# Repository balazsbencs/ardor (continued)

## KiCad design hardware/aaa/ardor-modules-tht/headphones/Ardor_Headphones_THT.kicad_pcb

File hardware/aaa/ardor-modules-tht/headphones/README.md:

# Stereo headphones / LM386 / relay mute

T1 hand-assembly PCB: 96 × 84 mm. **Unbuilt engineering prototype.**

[KiCad project](Ardor_Headphones_THT.kicad_pro) · [Manual BOM](BOM.csv) · [Schematic](review/schematic.pdf) · [Bare-board Gerbers](assembly/Ardor_Headphones_THT-Gerbers.zip)

Supply 5 V / **150 mA** and use 32–300 Ω headphones. Fit two **LM386N-1/NOPB** DIP-8 amplifiers, **G5V-2-H1 DC5** high-sensitivity DPDT relay, and onsemi 2N3904BU. Do not substitute LM386N-4 or the standard non-H1 relay: their operating conditions differ. Keep LM386 gain pins 1 and 8 open. No SMD IC or charge pump is present.

Input limit is 1 Vrms. The 39 kΩ/1 kΩ divider and nominal gain-20 amplifier give about 0.49 unloaded gain. R631/R632 provide 2.2 Ω output isolation; C651/C652 are 470 µF / 16 V, with positive toward the amplifiers. Their can diameter must be at most 8 mm with 3.5 mm lead spacing. C631/C632 bypass the internal references. The 10 Ω/47 nF output Zobel networks must be fitted. Both amplifiers remain powered when muted.

**Keep HP_ENABLE LOW for at least five seconds after stable supply/audio; mute before powering down.** HIGH is 3.3 V and draws approximately 5 mA. This timing is supplied by the host, not an onboard timer. R641/R642 are 1 kΩ bleeders which let the output coupling capacitors charge while the relay grounds the panel channels. Switching early can produce a loud transient. The relay commons are panel left/right, NC contacts ground them, and NO contacts select the AC-coupled audio.

Commission into separate **32 Ω dummy resistors**, with no headphones connected. Check about 2.5 V at U601/U602 pin 5, correct capacitor polarity, grounded panel outputs when muted, and settled near-zero DC at the relay's audio feeds before enabling. Capture startup, enable, disable and power-down waveforms, including host reset/disconnect. Measure gain, 20 Hz–20 kHz response, clipping, channel separation, hum, hiss and thermal behavior. This DIY design has different noise/distortion characteristics from M1's dedicated headphone IC. Begin listening at low host volume only after these checks pass.

## Connector pin assignments

Directions are relative to this board. Standard header square pads identify pin 1. Read reference and pin numbers from the back silkscreen; mirrored CAD exports are labelled as back views.

### J101 — 5V POWER + ENABLE INPUT

| Pin | Net | Direction | Connect to |
|---|---|---|---|
| 1 | +5V | POWER INPUT | Positive output of the matching regulated supply. |
| 2 | GND | GROUND | Host or cable ground / 0 V. |
| 3 | HP_ENABLE | CONTROL INPUT | Host control output. Keep LOW until audio and supply are stable. |

### J102 — STEREO AUDIO INPUT FROM SOURCE

| Pin | Net | Direction | Connect to |
|---|---|---|---|
| 1 | AUDIO_L | INPUT | DAC/codec left audio output, <=1 Vrms. |
| 2 | GND | GROUND | Host or cable ground / 0 V. |
| 3 | AUDIO_R | INPUT | DAC/codec right audio output, <=1 Vrms. |

### J602 — STEREO HEADPHONE AUDIO OUTPUT

| Pin | Net | Direction | Connect to |
|---|---|---|---|
| 1 | HP_L | OUTPUT | TRS socket tip; headphones >=32 ohm. |
| 2 | HP_R | OUTPUT | TRS socket ring; headphones >=32 ohm. |
| 3 | GND | GROUND | TRS socket sleeve; enclosure bond. |

## Assembly and files

Fit low-profile axial parts first, then sockets/headers and radial capacitors. Match diode bands, electrolytic polarity and IC notches to the PCB. Install the ICs or ADC breakout last. H1/H2 are 2.2 mm nonplated M2 mounting holes, not electrical terminals. Check enclosure clearance and capacitor/socket height: these boards are larger than M1.

Use the manual BOM and the bare-board Gerber/drill ZIP. There is no SMT assembly order. Front silkscreen shows component references; the front fabrication drawing shows package outlines and orientation; use the BOM for values. Back silk includes port functions and pin numbers. Native checks and package manifests are under `verification/`; they do not replace prototype measurements.

[Assembly accessories](assembly/accessories.csv) list sockets, shunts and panel items in addition to the PCB component BOM.

[Family guide](../README.md) · [Substitution sources](../SOURCES.md) · [Native validation](verification/validation.json)

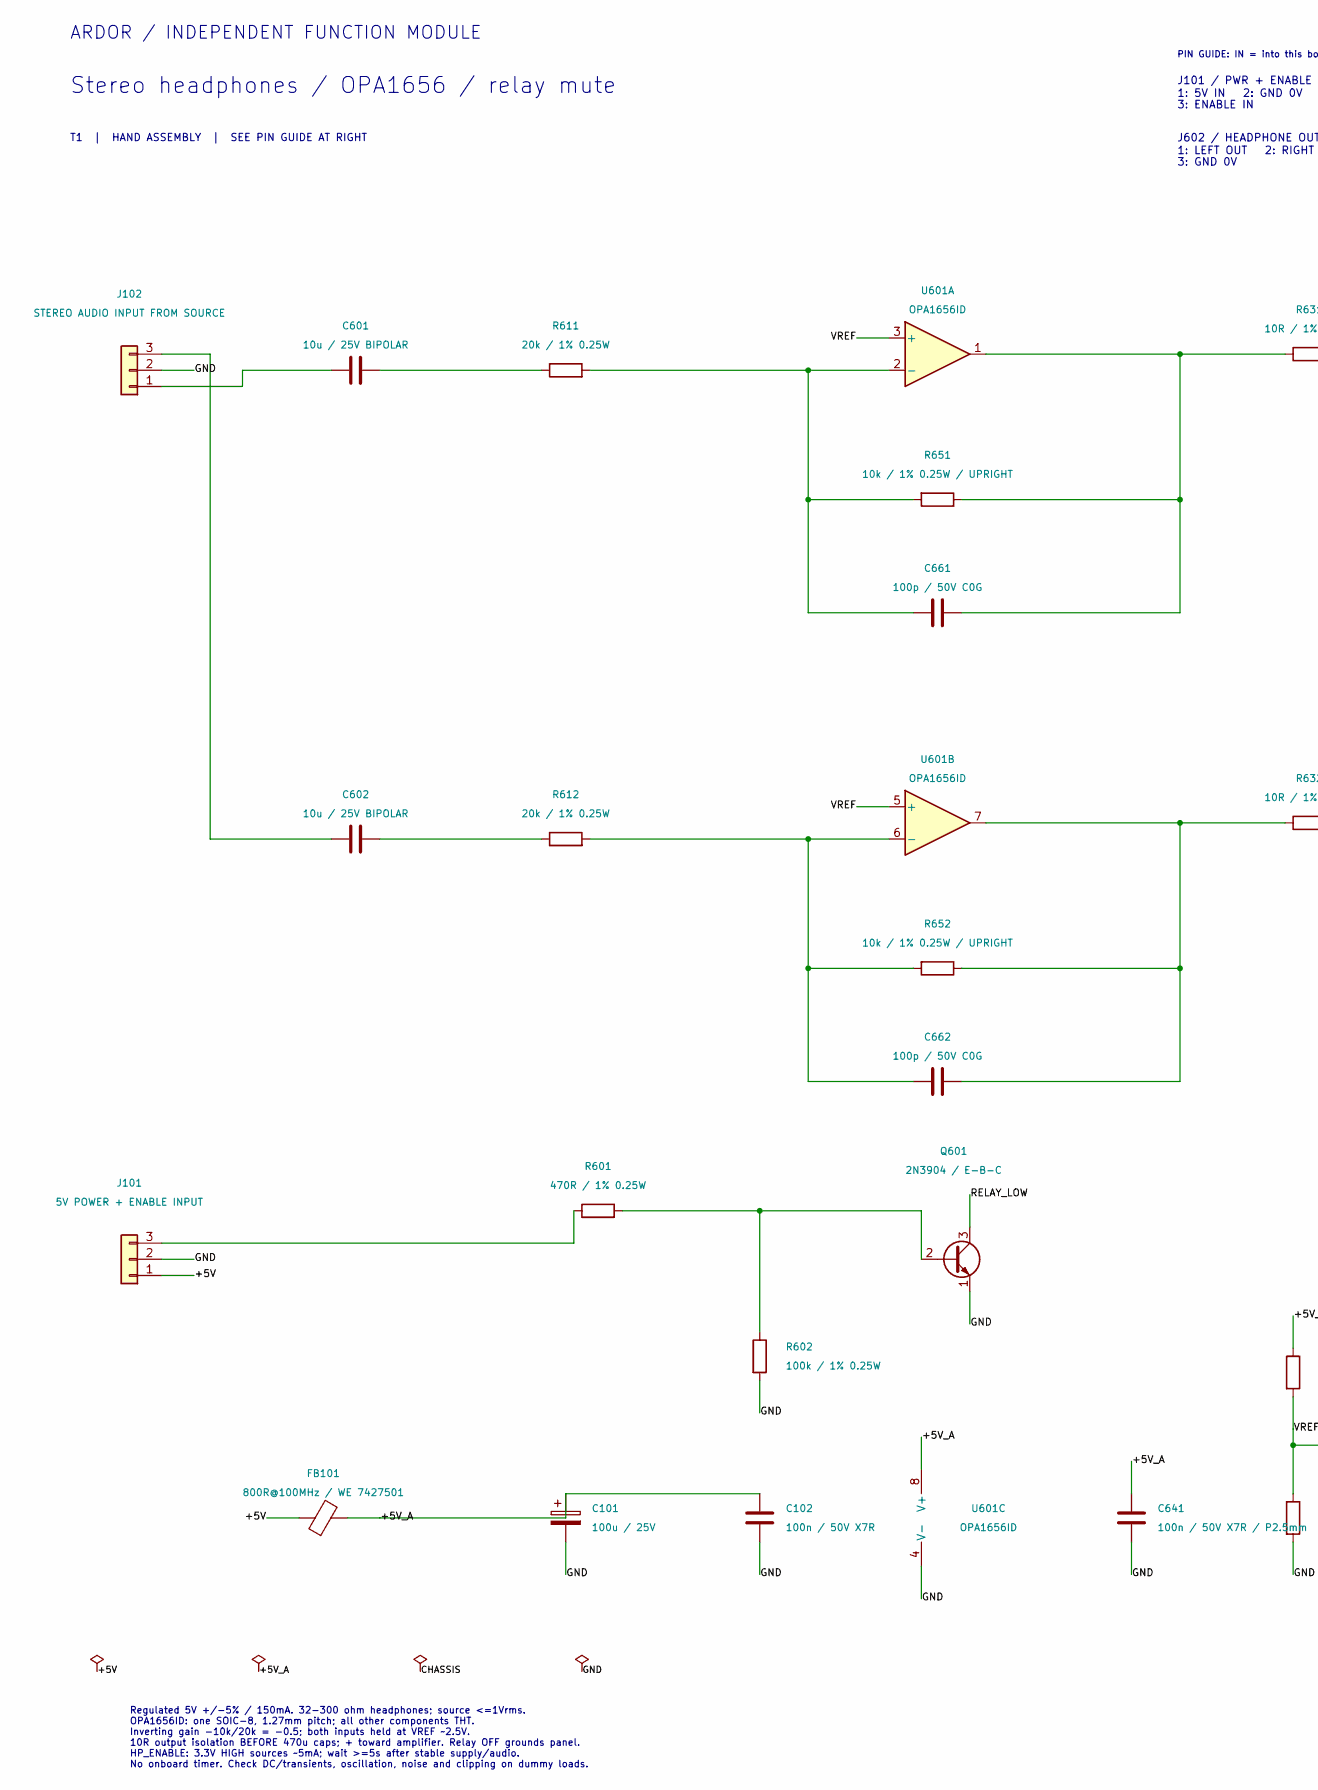
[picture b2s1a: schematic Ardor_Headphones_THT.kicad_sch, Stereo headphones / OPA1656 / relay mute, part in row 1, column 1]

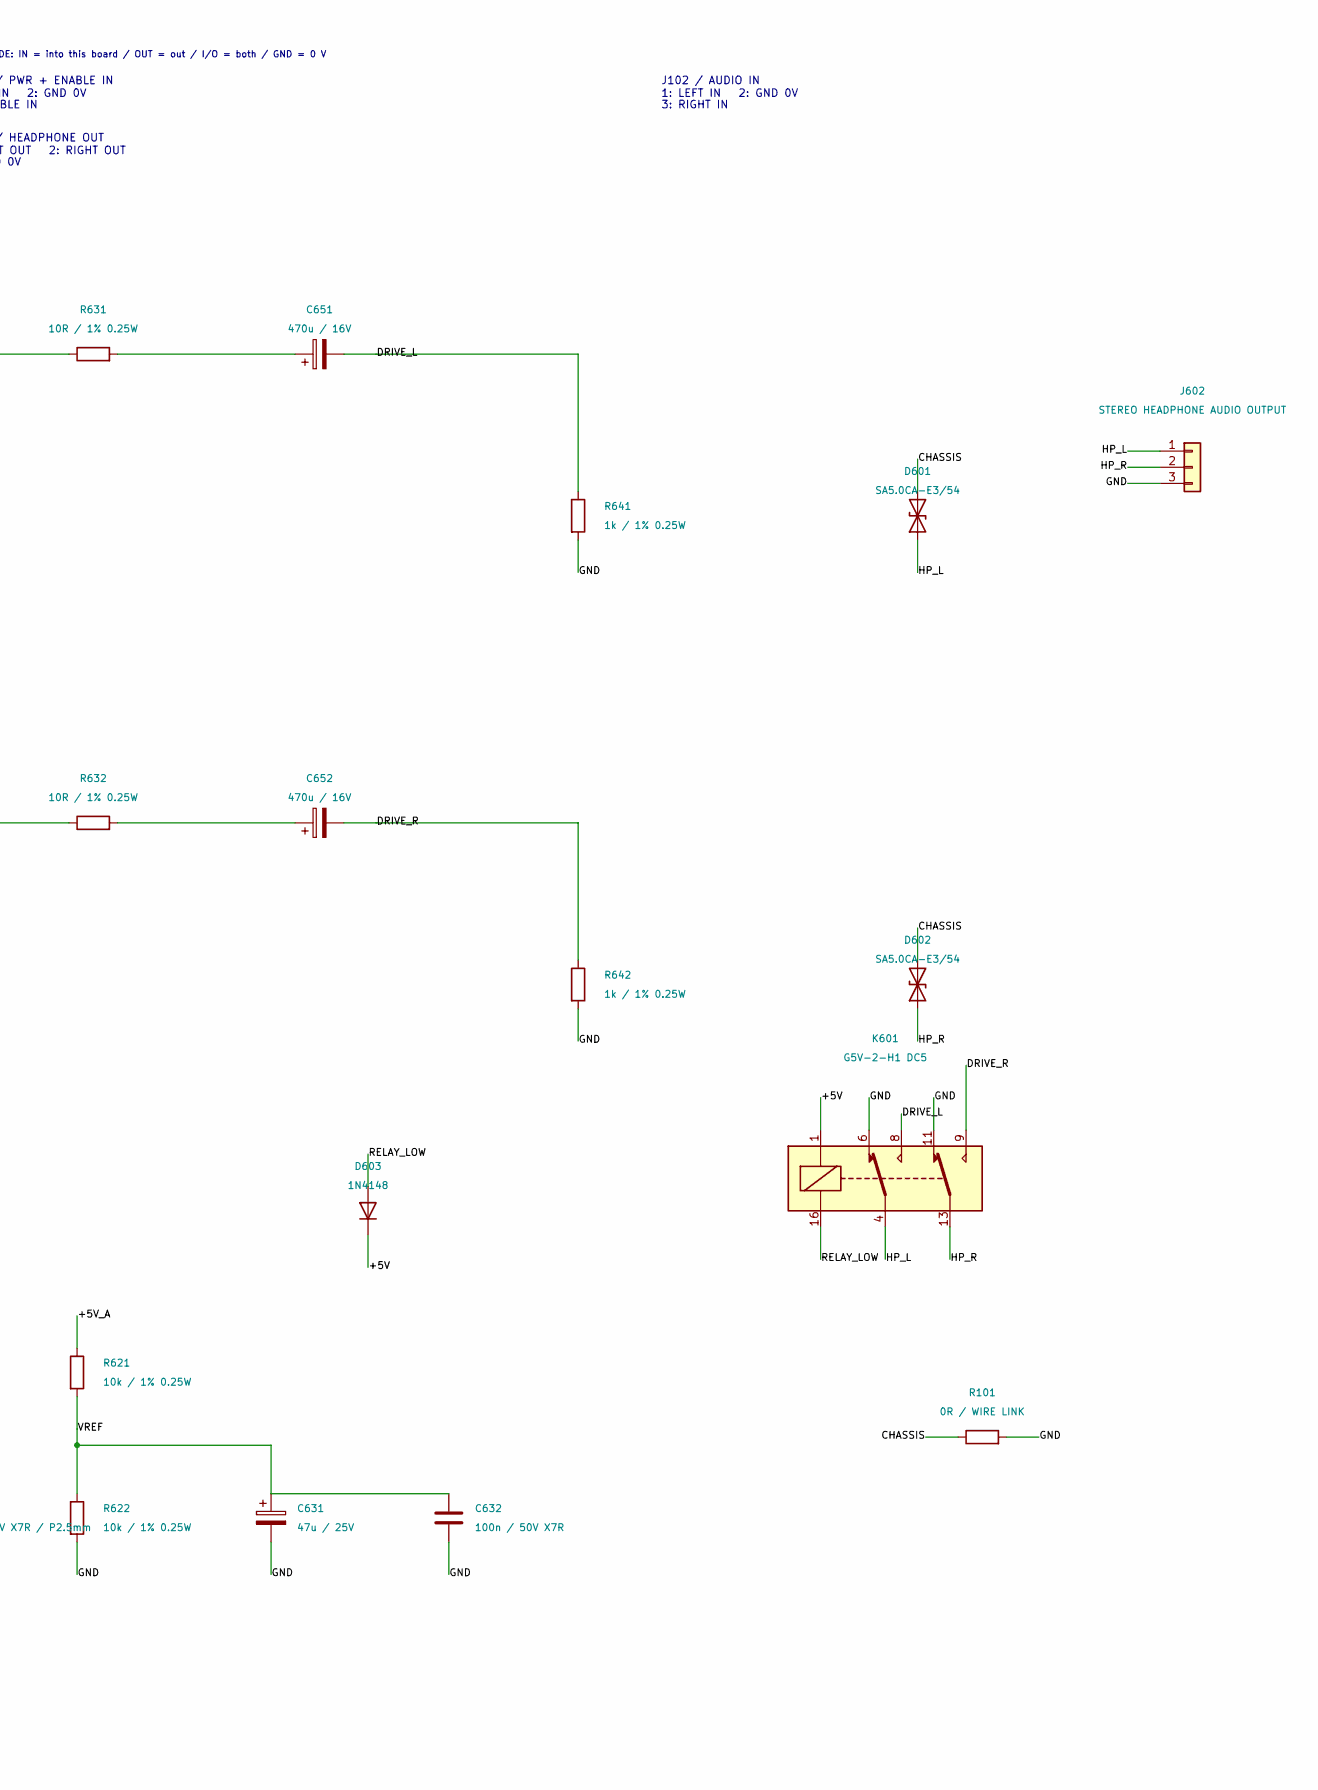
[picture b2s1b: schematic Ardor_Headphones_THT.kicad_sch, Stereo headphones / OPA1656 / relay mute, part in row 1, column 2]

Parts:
C101: 100u / 25V; CP_Radial_D6.3mm_P2.50mm; MPN 100u / 25V
C102, C632: 100n / 50V X7R; C_Disc_D5.0mm_W2.5mm_P5.00mm; MPN 100n / 50V X7R
C601, C602: 10u / 25V BIPOLAR; CP_Bipolar_D6.3mm_P2.50mm; MPN Nichicon UES1E100MDM
C631: 47u / 25V; CP_Radial_D6.3mm_P2.50mm; MPN 47u / 25V
C641: 100n / 50V X7R / P2.5mm; C_Disc_D3.8mm_W2.6mm_P2.50mm; MPN 100nF 50V X7R radial, D<=3.8mm W<=2.6mm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
C651, C652: 470u / 16V; CP_Radial_D8.0mm_P3.50mm; MPN 470u / 16V
C661, C662: 100p / 50V C0G; C_Disc_D5.0mm_W2.5mm_P5.00mm; MPN 100p / 50V C0G
D601, D602: SA5.0CA-E3/54; D_DO-15_P10.16mm_Horizontal; MPN Vishay SA5.0CA-E3/54
D603: 1N4148; D_DO-35_SOD27_P7.62mm_Horizontal; MPN Vishay 1N4148-TAP
FB101: 800R@100MHz / WE 7427501; Ferrite_WE_7427501_P15.24mm; MPN Wurth Elektronik 7427501
J101: 5V POWER + ENABLE INPUT; PinHeader_1x03_P2.54mm_Vertical; MPN PinHeader_1x03_P2.54mm_Vertical
J102: STEREO AUDIO INPUT FROM SOURCE; PinHeader_1x03_P2.54mm_Vertical; MPN PinHeader_1x03_P2.54mm_Vertical
J602: STEREO HEADPHONE AUDIO OUTPUT; PinHeader_1x03_P2.54mm_Vertical; MPN PinHeader_1x03_P2.54mm_Vertical
K601: G5V-2-H1 DC5; Relay_DPDT_Omron_G5V-2; MPN Omron G5V-2-H1 DC5
Q601: 2N3904 / E-B-C; TO-92_Inline_Wide; MPN onsemi 2N3904BU
R101: 0R / WIRE LINK; R_Axial_DIN0207_L6.3mm_D2.5mm_P10.16mm_Horizontal; MPN 0R / WIRE LINK
R601: 470R / 1% 0.25W; R_Axial_DIN0207_L6.3mm_D2.5mm_P10.16mm_Horizontal; MPN 470R / 1% 0.25W
R602: 100k / 1% 0.25W; R_Axial_DIN0207_L6.3mm_D2.5mm_P10.16mm_Horizontal; MPN 100k / 1% 0.25W
R611, R612: 20k / 1% 0.25W; R_Axial_DIN0207_L6.3mm_D2.5mm_P10.16mm_Horizontal; MPN 20k / 1% 0.25W
R621, R622: 10k / 1% 0.25W; R_Axial_DIN0207_L6.3mm_D2.5mm_P10.16mm_Horizontal; MPN 10k / 1% 0.25W
R631, R632: 10R / 1% 0.25W; R_Axial_DIN0207_L6.3mm_D2.5mm_P10.16mm_Horizontal; MPN 10R / 1% 0.25W
R641, R642: 1k / 1% 0.25W; R_Axial_DIN0207_L6.3mm_D2.5mm_P10.16mm_Horizontal; MPN 1k / 1% 0.25W
R651, R652: 10k / 1% 0.25W / UPRIGHT; R_Axial_DIN0207_L6.3mm_D2.5mm_P2.54mm_Vertical; MPN 10k / 1% 0.25W / UPRIGHT
U601: OPA1656ID; SOIC-8_3.9x4.9mm_P1.27mm; MPN Texas Instruments OPA1656ID

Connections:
/+5V: D603.1 (K), FB101.1, J101.1, K601.1
/+5V_A: C101.1, C102.1, C641.1, FB101.2, R621.1, U601.8 (V+)
/CHASSIS: D601.2 (A2), D602.2 (A2), R101.1
/DRIVE_L: C651.2, K601.8, R641.1
/DRIVE_R: C652.2, K601.9, R642.1
/GND: C101.2, C102.2, C631.2, C632.2, C641.2, J101.2, J102.2, J602.3, K601.6, K601.11, Q601.1 (E), R101.2, R602.2, R622.2, R641.2, R642.2, U601.4 (V-)
/HP_L: D601.1 (A1), J602.1, K601.4
/HP_R: D602.1 (A1), J602.2, K601.13
/RELAY_LOW: D603.2 (A), K601.16, Q601.3 (C)
/VREF: C631.1, C632.1, R621.2, R622.1, U601.3 (+), U601.5 (+)
unnamed: C601.2, R611.1
unnamed: C602.2, R612.1
unnamed: C651.1, R631.2
unnamed: C652.1, R632.2
unnamed: C661.1, R631.1, R651.1, U601.1
unnamed: C662.1, R632.1, R652.1, U601.7
unnamed: J101.3, R601.1
unnamed: C601.1, J102.1
unnamed: C602.1, J102.3
unnamed: Q601.2 (B), R601.2, R602.1
unnamed: C661.2, R611.2, R651.2, U601.2 (-)
unnamed: C662.2, R612.2, R652.2, U601.6 (-)

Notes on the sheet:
ARDOR / INDEPENDENT FUNCTION MODULE
Stereo headphones / OPA1656 / relay mute
T1 | HAND ASSEMBLY | SEE PIN GUIDE AT RIGHT
Regulated 5V +/-5% / 150mA. 32-300 ohm headphones; source <=1Vrms. OPA1656ID: one SOIC-8, 1.27mm pitch; all other components THT. Inverting gain -10k/20k = -0.5; both inputs held at VREF ~2.5V. 10R output isolation BEFORE 470u caps; + toward amplifier. Relay OFF grounds panel. HP_ENABLE: 3.3V HIGH 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
PIN GUIDE: IN = into this board / OUT = out / I/O = both / GND = 0 V
J101 / PWR + ENABLE IN
1: 5V IN 2: GND 0V
3: ENABLE IN
J102 / AUDIO IN
1: LEFT IN 2: GND 0V
3: RIGHT IN
J602 / HEADPHONE OUT
1: LEFT OUT 2: RIGHT OUT
3: GND 0V

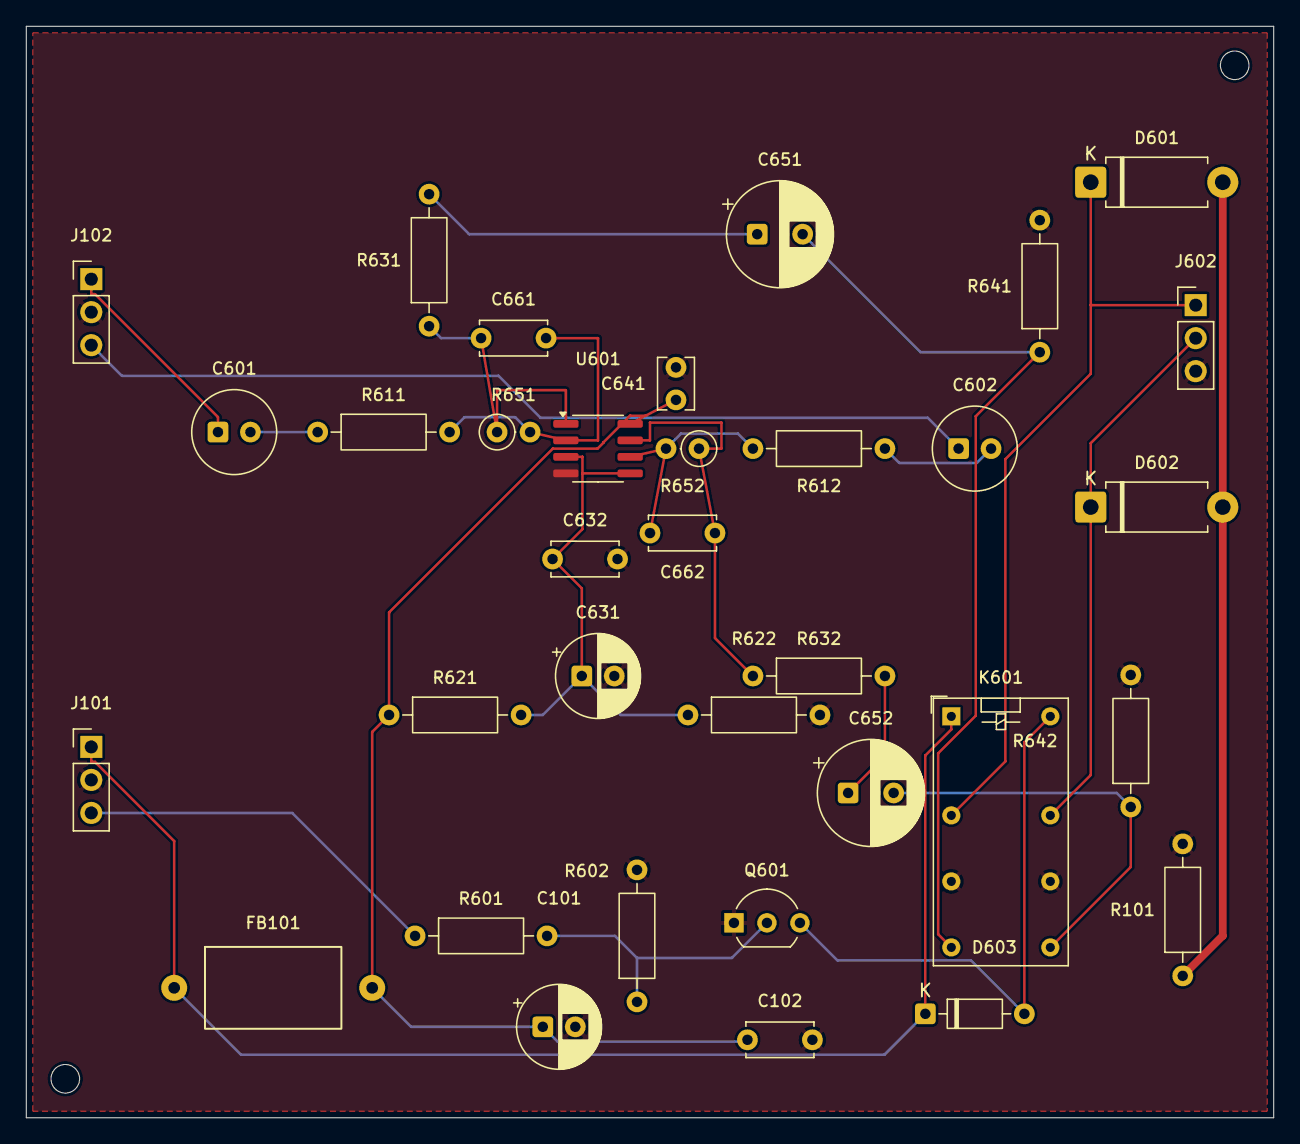
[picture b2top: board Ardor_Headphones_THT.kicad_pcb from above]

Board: 2 copper layers, 96.0 x 84.0 mm, 36 parts (0 on the bottom side), 22 nets.

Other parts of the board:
H1, H2: MountingHole_2.2mm_M2

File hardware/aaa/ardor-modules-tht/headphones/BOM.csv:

Reference,Value,Footprint,Purchasing specification,Assembly
J102,STEREO AUDIO INPUT FROM SOURCE,Connector_PinHeader_2.54mm:PinHeader_1x03_P2.54mm_Vertical,PinHeader_1x03_P2.54mm_Vertical,THT manual
J101,5V POWER + ENABLE INPUT,Connector_PinHeader_2.54mm:PinHeader_1x03_P2.54mm_Vertical,PinHeader_1x03_P2.54mm_Vertical,THT manual
J602,STEREO HEADPHONE AUDIO OUTPUT,Connector_PinHeader_2.54mm:PinHeader_1x03_P2.54mm_Vertical,PinHeader_1x03_P2.54mm_Vertical,THT manual
FB101,800R@100MHz / WE 7427501,Ardor_THT:Ferrite_WE_7427501_P15.24mm,Wurth Elektronik 7427501,THT manual
C101,100u / 25V,Capacitor_THT:CP_Radial_D6.3mm_P2.50mm,100u / 25V,THT manual
C102,100n / 50V X7R,Capacitor_THT:C_Disc_D5.0mm_W2.5mm_P5.00mm,100n / 50V X7R,THT manual
C601,10u / 25V BIPOLAR,Ardor_THT:CP_Bipolar_D6.3mm_P2.50mm,Nichicon UES1E100MDM,THT manual
R611,20k / 1% 0.25W,Resistor_THT:R_Axial_DIN0207_L6.3mm_D2.5mm_P10.16mm_Horizontal,20k / 1% 0.25W,THT manual
U601,OPA1656ID,Package_SO:SOIC-8_3.9x4.9mm_P1.27mm,Texas Instruments OPA1656ID,SMD manual / SOIC-8 1.27mm pitch
R651,10k / 1% 0.25W / UPRIGHT,Resistor_THT:R_Axial_DIN0207_L6.3mm_D2.5mm_P2.54mm_Vertical,10k / 1% 0.25W / UPRIGHT,THT manual
C661,100p / 50V C0G,Capacitor_THT:C_Disc_D5.0mm_W2.5mm_P5.00mm,100p / 50V C0G,THT manual
R631,10R / 1% 0.25W,Resistor_THT:R_Axial_DIN0207_L6.3mm_D2.5mm_P10.16mm_Horizontal,10R / 1% 0.25W,THT manual
C651,470u / 16V,Capacitor_THT:CP_Radial_D8.0mm_P3.50mm,470u / 16V,THT manual
R641,1k / 1% 0.25W,Resistor_THT:R_Axial_DIN0207_L6.3mm_D2.5mm_P10.16mm_Horizontal,1k / 1% 0.25W,THT manual
D601,1.5KE6.8CA,Ardor_THT:D_TVS_DC_1.5KE_P15.24mm,DC Components 1.5KE6.8CA (HESTORE 100.430.71),THT manual
C602,10u / 25V BIPOLAR,Ardor_THT:CP_Bipolar_D6.3mm_P2.50mm,Nichicon UES1E100MDM,THT manual
R612,20k / 1% 0.25W,Resistor_THT:R_Axial_DIN0207_L6.3mm_D2.5mm_P10.16mm_Horizontal,20k / 1% 0.25W,THT manual
R652,10k / 1% 0.25W / UPRIGHT,Resistor_THT:R_Axial_DIN0207_L6.3mm_D2.5mm_P2.54mm_Vertical,10k / 1% 0.25W / UPRIGHT,THT manual
C662,100p / 50V C0G,Capacitor_THT:C_Disc_D5.0mm_W2.5mm_P5.00mm,100p / 50V C0G,THT manual
R632,10R / 1% 0.25W,Resistor_THT:R_Axial_DIN0207_L6.3mm_D2.5mm_P10.16mm_Horizontal,10R / 1% 0.25W,THT manual
C652,470u / 16V,Capacitor_THT:CP_Radial_D8.0mm_P3.50mm,470u / 16V,THT manual
R642,1k / 1% 0.25W,Resistor_THT:R_Axial_DIN0207_L6.3mm_D2.5mm_P10.16mm_Horizontal,1k / 1% 0.25W,THT manual
D602,1.5KE6.8CA,Ardor_THT:D_TVS_DC_1.5KE_P15.24mm,DC Components 1.5KE6.8CA (HESTORE 100.430.71),THT manual
C641,100n / 50V X7R / P2.5mm,Capacitor_THT:C_Disc_D3.8mm_W2.6mm_P2.50mm,"100nF 50V X7R radial, D<=3.8mm W<=2.6mm P2.5mm",THT manual
R621,10k / 1% 0.25W,Resistor_THT:R_Axial_DIN0207_L6.3mm_D2.5mm_P10.16mm_Horizontal,10k / 1% 0.25W,THT manual
R622,10k / 1% 0.25W,Resistor_THT:R_Axial_DIN0207_L6.3mm_D2.5mm_P10.16mm_Horizontal,10k / 1% 0.25W,THT manual
C631,47u / 25V,Capacitor_THT:CP_Radial_D6.3mm_P2.50mm,47u / 25V,THT manual
C632,100n / 50V X7R,Capacitor_THT:C_Disc_D5.0mm_W2.5mm_P5.00mm,100n / 50V X7R,THT manual
K601,G5V-2-H1 DC5,Relay_THT:Relay_DPDT_Omron_G5V-2,Omron G5V-2-H1 DC5,THT manual
Q601,2N3904 / E-B-C,Package_TO_SOT_THT:TO-92_Inline_Wide,onsemi 2N3904BU,THT manual
R601,470R / 1% 0.25W,Resistor_THT:R_Axial_DIN0207_L6.3mm_D2.5mm_P10.16mm_Horizontal,470R / 1% 0.25W,THT manual
R602,100k / 1% 0.25W,Resistor_THT:R_Axial_DIN0207_L6.3mm_D2.5mm_P10.16mm_Horizontal,100k / 1% 0.25W,THT manual
D603,1N4148,Diode_THT:D_DO-35_SOD27_P7.62mm_Horizontal,Vishay 1N4148-TAP,THT manual
R101,0R / WIRE LINK,Resistor_THT:R_Axial_DIN0207_L6.3mm_D2.5mm_P10.16mm_Horizontal,0R / WIRE LINK,THT manual

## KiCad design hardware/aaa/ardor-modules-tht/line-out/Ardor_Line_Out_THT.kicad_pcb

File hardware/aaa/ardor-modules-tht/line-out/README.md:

# Mono line output / relay mute / internal amp feed / HAND ASSEMBLY

T1 hand-assembly PCB: 115 × 85 mm. **Unbuilt engineering prototype.**

[KiCad project](Ardor_Line_Out_THT.kicad_pro) · [Manual BOM](BOM.csv) · [Schematic](review/schematic.pdf) · [Bare-board Gerbers](assembly/Ardor_Line_Out_THT-Gerbers.zip)

Supply 5 V / 50 mA. Fit MCP6022-I/P, **onsemi 2N3904BU** (E1/B2/C3), and **Omron G5V-1 DC5**. The 470 Ω base resistor means LINE_ENABLE draws approximately 5 mA from a 3.3 V HIGH; confirm the host GPIO can source this current. Fit a banded 1N4148 flyback diode, cathode toward +5 V. C501 is polarized: its positive end goes toward the audio buffer. C401/C502 are bipolar.

The mono input limit is 1 Vrms. The line output requires at least 10 kΩ load; the internal AMP_FEED requires at least 100 kΩ. J502 carries a signal for an external amplifier; it cannot drive a speaker. Relay OFF grounds the panel tip and disconnects the source. Relay ON connects the AC-coupled line signal. This is a mute, not true bypass. The internal amp feed is not relay-muted.

Hold LINE_ENABLE LOW until power/audio have settled; allowing five seconds also settles the line coupling capacitor. Mute before power-down. Commission with the panel unplugged: check the 5 V rail, about 2.5 V internal bias, GPIO base current, relay coil voltage and contact behavior. With the relay off, verify the panel output is grounded. After settling, enable and measure external DC and unity audio into a 10 kΩ dummy load. Check startup/power-down transients before connecting an amplifier.

## Connector pin assignments

Directions are relative to this board. Standard header square pads identify pin 1. Read reference and pin numbers from the back silkscreen; mirrored CAD exports are labelled as back views.

### J101 — 5V POWER + ENABLE INPUT

| Pin | Net | Direction | Connect to |
|---|---|---|---|
| 1 | +5V | POWER INPUT | Positive output of the matching regulated supply. |
| 2 | GND | GROUND | Host or cable ground / 0 V. |
| 3 | LINE_ENABLE | CONTROL INPUT | Host control output. Keep LOW until audio and supply are stable. |

### J102 — MONO AUDIO INPUT FROM SOURCE

| Pin | Net | Direction | Connect to |
|---|---|---|---|
| 1 | AUDIO_IN | INPUT | Mono DAC/codec audio output, <=1 Vrms. |
| 2 | GND | GROUND | Host or cable ground / 0 V. |

### J503 — LINE AUDIO OUTPUT TO TS SOCKET

| Pin | Net | Direction | Connect to |
|---|---|---|---|
| 1 | LINE_JACK | OUTPUT | TS socket tip; line load >=10k. Grounded when relay is off. |
| 2 | GND | GROUND | TS socket sleeve; enclosure bond. |

### J502 — AUDIO OUTPUT TO AMP INPUT

| Pin | Net | Direction | Connect to |
|---|---|---|---|
| 1 | AMP_FEED | OUTPUT | Signal input of a separate amplifier, >=100k. NOT a speaker. |
| 2 | GND | GROUND | Host or cable ground / 0 V. |

Audio signal only. Never connect a speaker here.

## Assembly and files

Fit low-profile axial parts first, then sockets/headers and radial capacitors. Match diode bands, electrolytic polarity and IC notches to the PCB. Install the ICs or ADC breakout last. H1/H2 are 2.2 mm nonplated M2 mounting holes, not electrical terminals. Check enclosure clearance and capacitor/socket height: these boards are larger than M1.

Use the manual BOM and the bare-board Gerber/drill ZIP. There is no SMT assembly order. Front silkscreen shows component references; the front fabrication drawing shows package outlines and orientation; use the BOM for values. Back silk includes port functions and pin numbers. Native checks and package manifests are under `verification/`; they do not replace prototype measurements.

[Assembly accessories](assembly/accessories.csv) list sockets, shunts and panel items in addition to the PCB component BOM.

[Family guide](../README.md) · [Substitution sources](../SOURCES.md) · [Native validation](verification/validation.json)

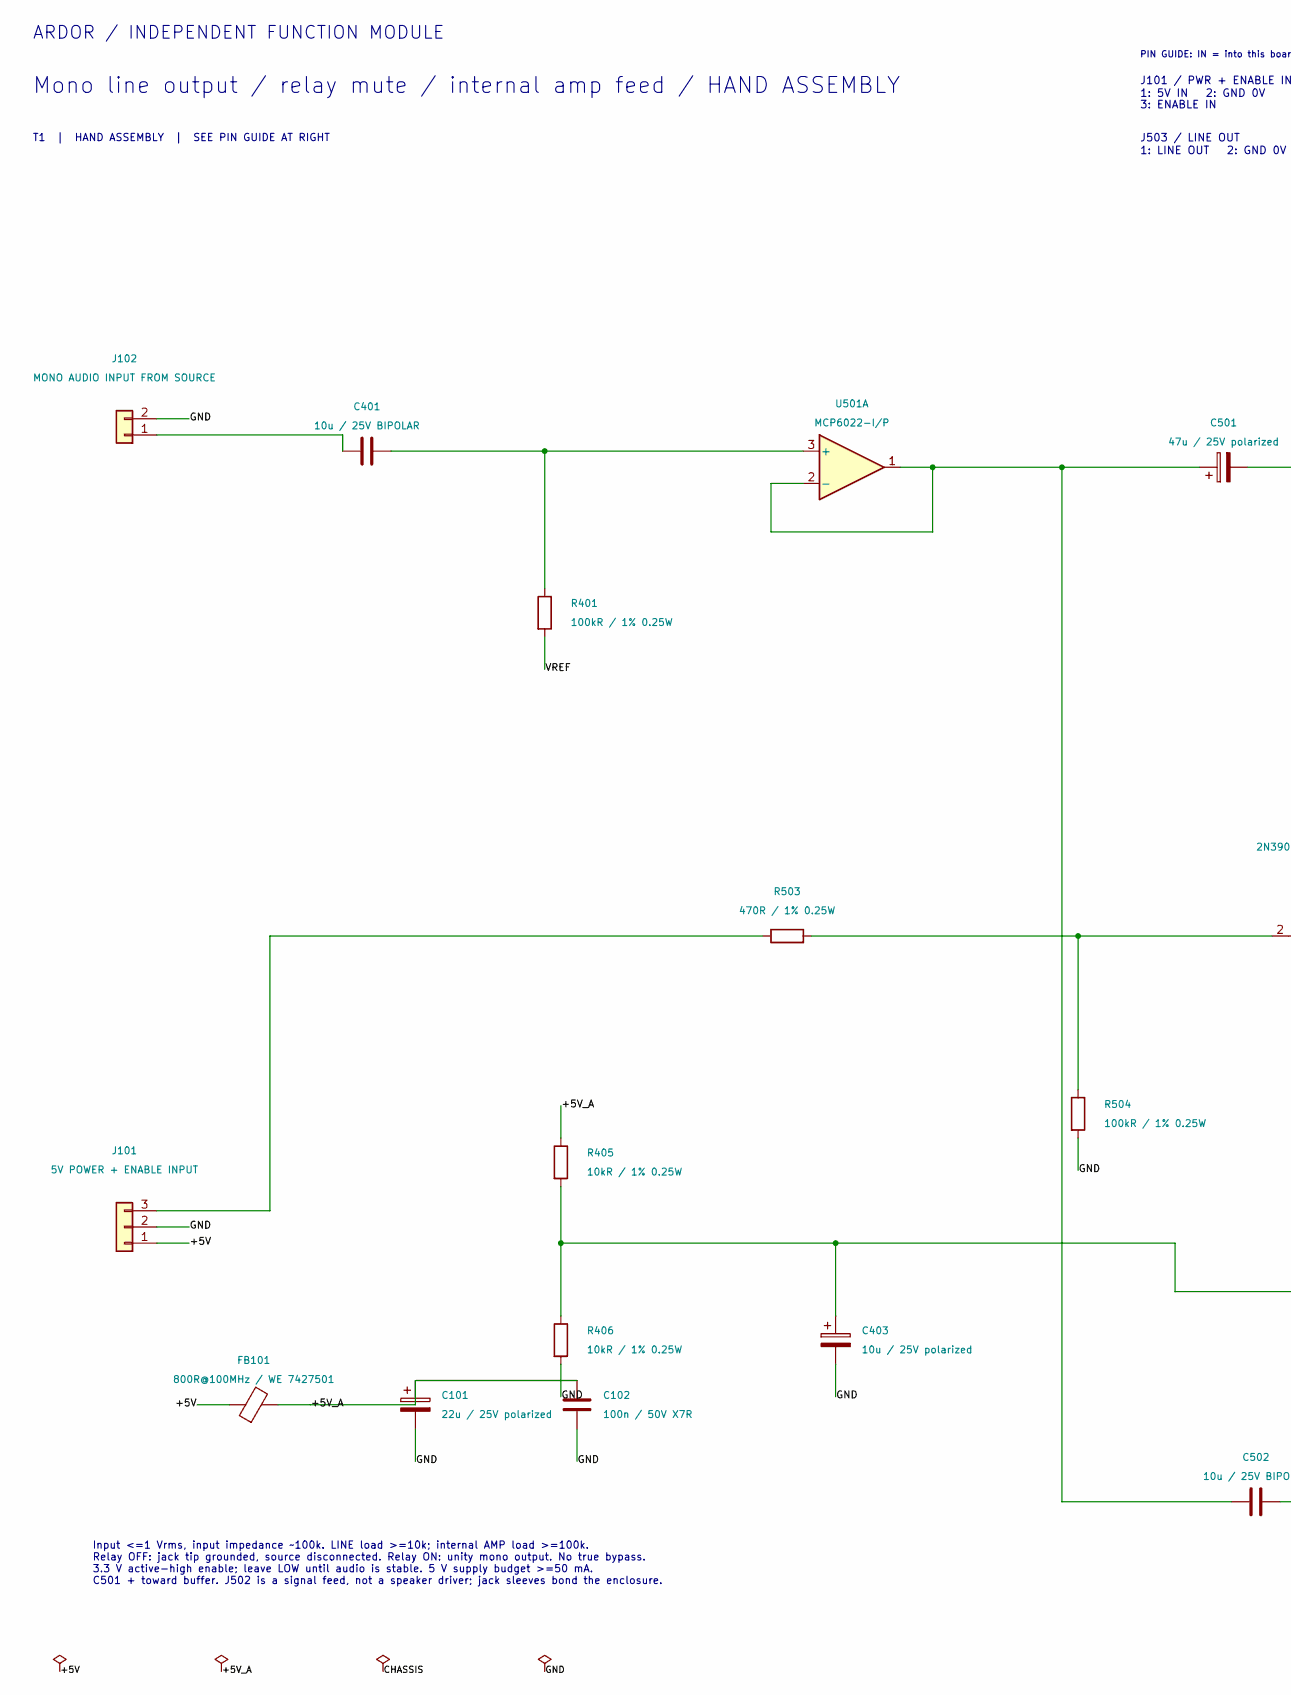
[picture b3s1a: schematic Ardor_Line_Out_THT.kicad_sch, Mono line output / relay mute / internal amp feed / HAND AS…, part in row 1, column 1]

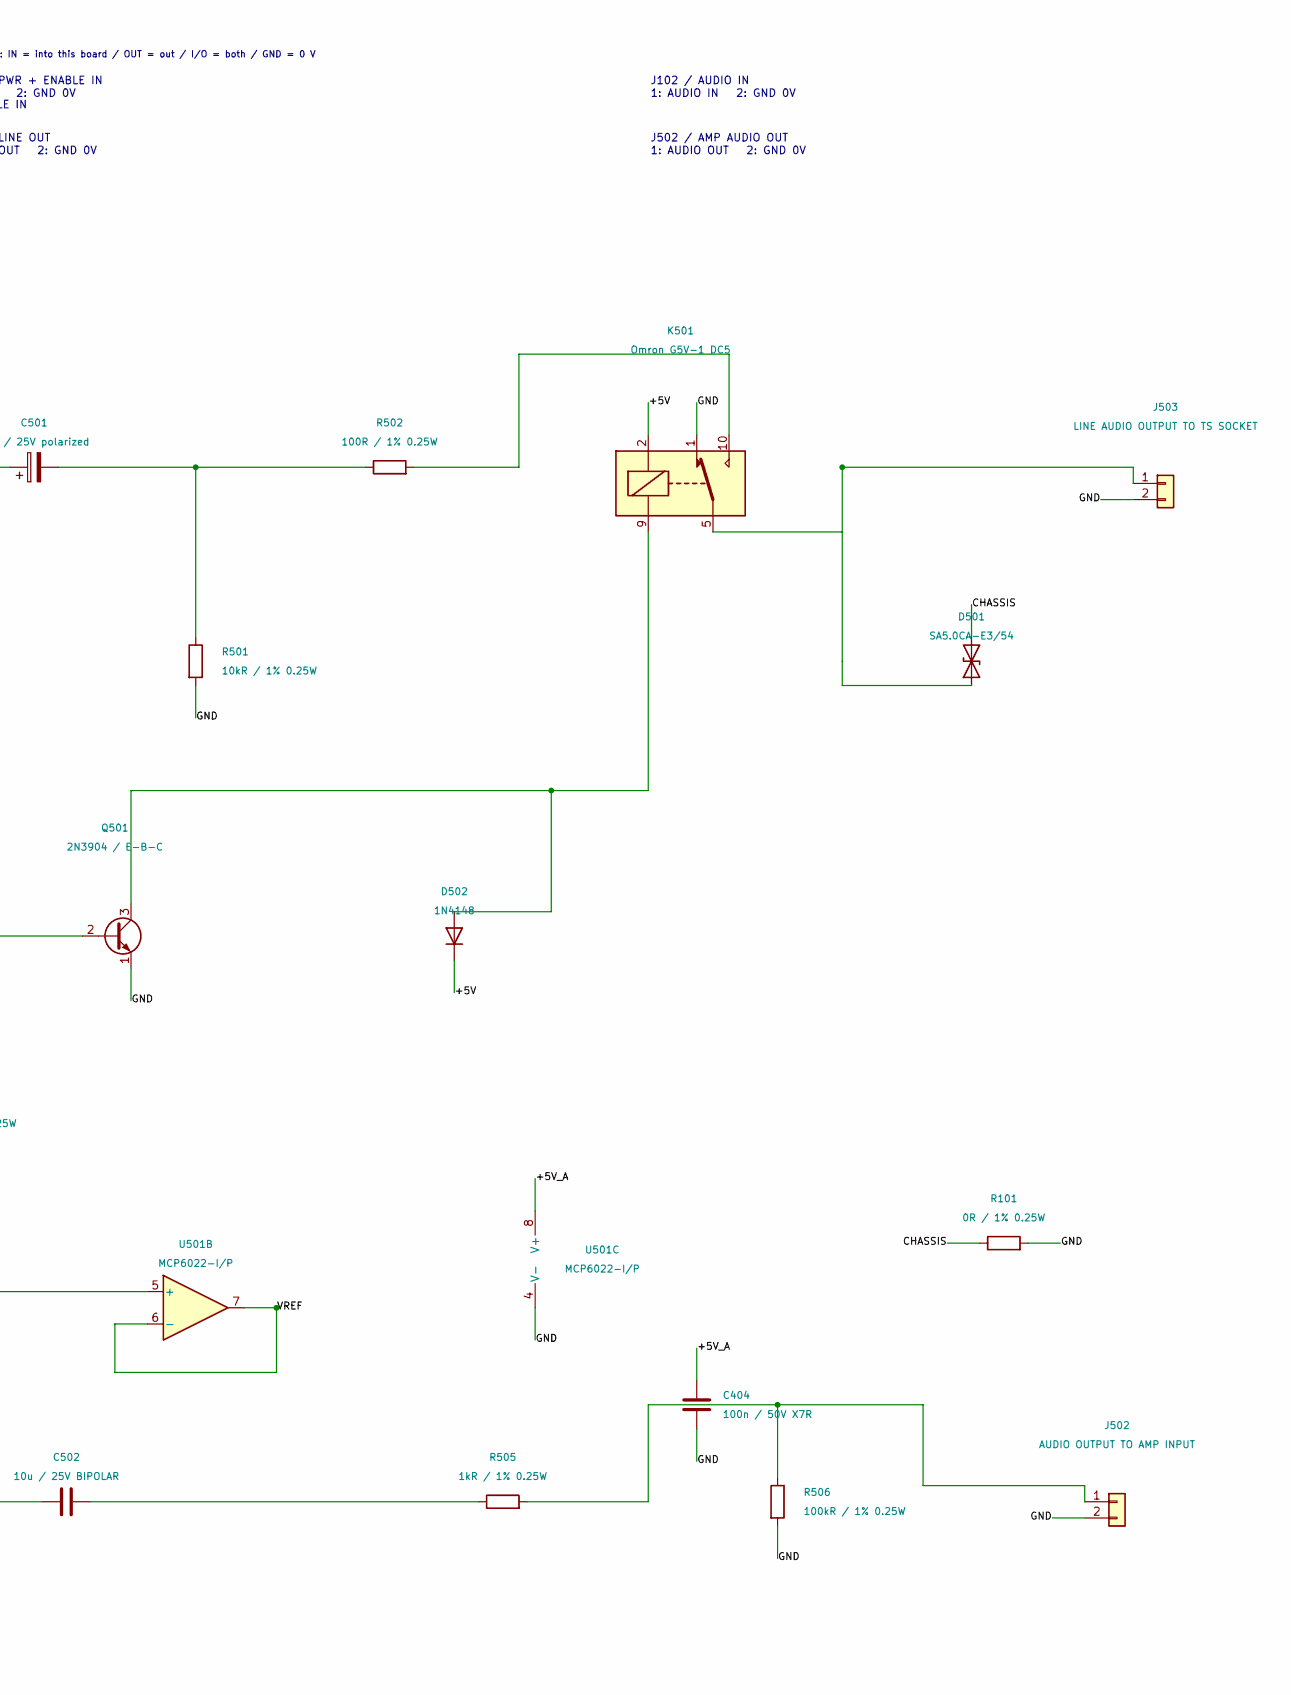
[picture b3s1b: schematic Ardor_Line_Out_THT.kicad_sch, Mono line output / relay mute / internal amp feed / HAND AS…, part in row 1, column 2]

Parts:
C101: 22u / 25V polarized; CP_Radial_D6.3mm_P2.50mm; MPN Radial electrolytic 22uF 25V, D<=6.3mm 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
C102, C404: 100n / 50V X7R; C_Disc_D5.0mm_W2.5mm_P5.00mm; MPN 100nF 50V X7R radial, 5mm lead pitch
C401, C502: 10u / 25V BIPOLAR; CP_Bipolar_D6.3mm_P2.50mm; MPN Nichicon UES1E100MDM
C403: 10u / 25V polarized; CP_Radial_D6.3mm_P2.50mm; MPN Radial electrolytic 10uF 25V, D<=6.3mm 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
C501: 47u / 25V polarized; CP_Radial_D6.3mm_P2.50mm; MPN Radial electrolytic 47uF 25V, D<=6.3mm 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
D501: SA5.0CA-E3/54; D_DO-15_P10.16mm_Horizontal; MPN Vishay SA5.0CA-E3/54
D502: 1N4148; D_DO-35_SOD27_P7.62mm_Horizontal; MPN Vishay 1N4148-TAP
FB101: 800R@100MHz / WE 7427501; Ferrite_WE_7427501_P15.24mm; MPN Wurth Elektronik 7427501
J101: 5V POWER + ENABLE INPUT; PinHeader_1x03_P2.54mm_Vertical; MPN PinHeader_1x03_P2.54mm_Vertical
J102: MONO AUDIO INPUT FROM SOURCE; PinHeader_1x02_P2.54mm_Vertical; MPN PinHeader_1x02_P2.54mm_Vertical
J502: AUDIO OUTPUT TO AMP INPUT; PinHeader_1x02_P2.54mm_Vertical; MPN PinHeader_1x02_P2.54mm_Vertical
J503: LINE AUDIO OUTPUT TO TS SOCKET; PinHeader_1x02_P2.54mm_Vertical; MPN PinHeader_1x02_P2.54mm_Vertical
K501: Omron G5V-1 DC5; Relay_SPDT_Omron_G5V-1; MPN Omron G5V-1 DC5
Q501: 2N3904 / E-B-C; TO-92_Inline_Wide; MPN onsemi 2N3904BU
R101: 0R / 1% 0.25W; R_Axial_DIN0207_L6.3mm_D2.5mm_P10.16mm_Horizontal; MPN Axial metal film 0Ω 1% 0.25W
R401, R504, R506: 100kR / 1% 0.25W; R_Axial_DIN0207_L6.3mm_D2.5mm_P10.16mm_Horizontal; MPN Axial metal film 100kΩ 1% 0.25W
R405, R406, R501: 10kR / 1% 0.25W; R_Axial_DIN0207_L6.3mm_D2.5mm_P10.16mm_Horizontal; MPN Axial metal film 10kΩ 1% 0.25W
R502: 100R / 1% 0.25W; R_Axial_DIN0207_L6.3mm_D2.5mm_P10.16mm_Horizontal; MPN Axial metal film 100Ω 1% 0.25W
R503: 470R / 1% 0.25W; R_Axial_DIN0207_L6.3mm_D2.5mm_P10.16mm_Horizontal; MPN Axial metal film 470Ω 1% 0.25W
R505: 1kR / 1% 0.25W; R_Axial_DIN0207_L6.3mm_D2.5mm_P10.16mm_Horizontal; MPN Axial metal film 1kΩ 1% 0.25W
U501: MCP6022-I/P; DIP-8_W7.62mm_Socket; MPN Microchip MCP6022-I/P

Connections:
/+5V: D502.1 (K), FB101.1, J101.1, K501.2
/+5V_A: C101.1, C102.1, C404.1, FB101.2, R405.1, U501.8 (V+)
/CHASSIS: D501.2 (A2), R101.1
/GND: C101.2, C102.2, C403.2, C404.2, J101.2, J102.2, J502.2, J503.2, K501.1, Q501.1 (E), R101.2, R406.2, R501.2, R504.2, R506.2, U501.4 (V-)
/VREF: R401.2, U501.6 (-), U501.7
unnamed: C501.2, R501.1, R502.1
unnamed: C502.2, R505.1
unnamed: D501.1 (A1), J503.1, K501.5, K501.6
unnamed: D502.2 (A), K501.9, Q501.3 (C)
unnamed: J101.3, R503.1
unnamed: C401.1, J102.1
unnamed: J502.1, R505.2, R506.1
unnamed: K501.10, R502.2
unnamed: Q501.2 (B), R503.2, R504.1
unnamed: C401.2, R401.1, U501.3 (+)
unnamed: C501.1, C502.1, U501.1, U501.2 (-)
unnamed: C403.1, R405.2, R406.1, U501.5 (+)

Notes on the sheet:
ARDOR / INDEPENDENT FUNCTION MODULE
Mono line output / relay mute / internal amp feed / HAND ASSEMBLY
T1 | HAND ASSEMBLY | SEE PIN GUIDE AT RIGHT
Input <=1 Vrms, input impedance ~100k. LINE load >=10k; internal AMP load >=100k. Relay OFF: jack tip grounded, source disconnected. Relay ON: unity mono output. No true bypass. 3.3 V active-high enable; leave LOW until audio is stable. 5 V supply budget >=50 mA. C501 + toward buffer. J502 is a sig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
PIN GUIDE: IN = into this board / OUT = out / I/O = both / GND = 0 V
J101 / PWR + ENABLE IN
1: 5V IN 2: GND 0V
3: ENABLE IN
J102 / AUDIO IN
1: AUDIO IN 2: GND 0V
J503 / LINE OUT
1: LINE OUT 2: GND 0V
J502 / AMP AUDIO OUT
1: AUDIO OUT 2: GND 0V

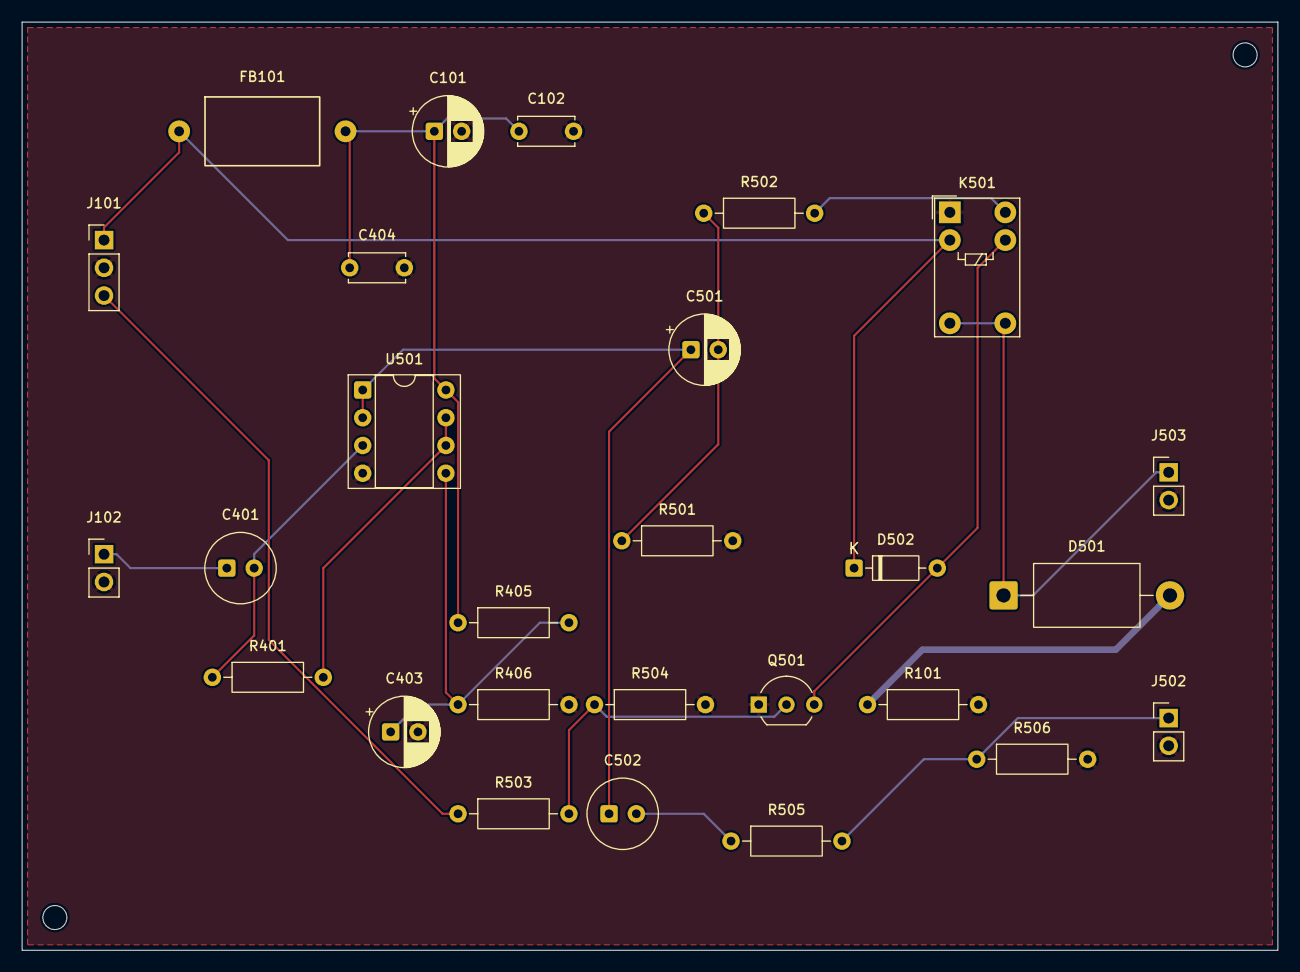
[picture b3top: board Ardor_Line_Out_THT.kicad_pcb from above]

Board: 2 copper layers, 115.0 x 85.0 mm, 29 parts (0 on the bottom side), 17 nets.

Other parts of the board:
H1, H2: MountingHole_2.2mm_M2

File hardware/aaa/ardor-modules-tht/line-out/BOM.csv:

Reference,Value,Footprint,Purchasing specification,Assembly
J102,MONO AUDIO INPUT FROM SOURCE,Connector_PinHeader_2.54mm:PinHeader_1x02_P2.54mm_Vertical,PinHeader_1x02_P2.54mm_Vertical,THT manual
J101,5V POWER + ENABLE INPUT,Connector_PinHeader_2.54mm:PinHeader_1x03_P2.54mm_Vertical,PinHeader_1x03_P2.54mm_Vertical,THT manual
J503,LINE AUDIO OUTPUT TO TS SOCKET,Connector_PinHeader_2.54mm:PinHeader_1x02_P2.54mm_Vertical,PinHeader_1x02_P2.54mm_Vertical,THT manual
J502,AUDIO OUTPUT TO AMP INPUT,Connector_PinHeader_2.54mm:PinHeader_1x02_P2.54mm_Vertical,PinHeader_1x02_P2.54mm_Vertical,THT manual
FB101,800R@100MHz / WE 7427501,Ardor_THT:Ferrite_WE_7427501_P15.24mm,Wurth Elektronik 7427501,THT manual
C101,22u / 25V polarized,Capacitor_THT:CP_Radial_D6.3mm_P2.50mm,"Radial electrolytic 22uF 25V, D<=6.3mm P2.5mm",THT manual
C102,100n / 50V X7R,Capacitor_THT:C_Disc_D5.0mm_W2.5mm_P5.00mm,"100nF 50V X7R radial, 5mm lead pitch",THT manual
C401,10u / 25V BIPOLAR,Ardor_THT:CP_Bipolar_D6.3mm_P2.50mm,Nichicon UES1E100MDM,THT manual
R401,100kR / 1% 0.25W,Resistor_THT:R_Axial_DIN0207_L6.3mm_D2.5mm_P10.16mm_Horizontal,Axial metal film 100kΩ 1% 0.25W,THT manual
U501,MCP6022-I/P,Package_DIP:DIP-8_W7.62mm_Socket,Microchip MCP6022-I/P,THT manual
C501,47u / 25V polarized,Capacitor_THT:CP_Radial_D6.3mm_P2.50mm,"Radial electrolytic 47uF 25V, D<=6.3mm P2.5mm",THT manual
R501,10kR / 1% 0.25W,Resistor_THT:R_Axial_DIN0207_L6.3mm_D2.5mm_P10.16mm_Horizontal,Axial metal film 10kΩ 1% 0.25W,THT manual
R502,100R / 1% 0.25W,Resistor_THT:R_Axial_DIN0207_L6.3mm_D2.5mm_P10.16mm_Horizontal,Axial metal film 100Ω 1% 0.25W,THT manual
K501,Omron G5V-1 DC5,Relay_THT:Relay_SPDT_Omron_G5V-1,Omron G5V-1 DC5,THT manual
D501,SA5.0CA-E3/54,Diode_THT:D_DO-15_P10.16mm_Horizontal,Vishay SA5.0CA-E3/54,THT manual
R101,0R / 1% 0.25W,Resistor_THT:R_Axial_DIN0207_L6.3mm_D2.5mm_P10.16mm_Horizontal,Axial metal film 0Ω 1% 0.25W,THT manual
Q501,2N3904 / E-B-C,Package_TO_SOT_THT:TO-92_Inline_Wide,onsemi 2N3904BU,THT manual
R503,470R / 1% 0.25W,Resistor_THT:R_Axial_DIN0207_L6.3mm_D2.5mm_P10.16mm_Horizontal,Axial metal film 470Ω 1% 0.25W,THT manual
R504,100kR / 1% 0.25W,Resistor_THT:R_Axial_DIN0207_L6.3mm_D2.5mm_P10.16mm_Horizontal,Axial metal film 100kΩ 1% 0.25W,THT manual
D502,1N4148,Diode_THT:D_DO-35_SOD27_P7.62mm_Horizontal,Vishay 1N4148-TAP,THT manual
R405,10kR / 1% 0.25W,Resistor_THT:R_Axial_DIN0207_L6.3mm_D2.5mm_P10.16mm_Horizontal,Axial metal film 10kΩ 1% 0.25W,THT manual
R406,10kR / 1% 0.25W,Resistor_THT:R_Axial_DIN0207_L6.3mm_D2.5mm_P10.16mm_Horizontal,Axial metal film 10kΩ 1% 0.25W,THT manual
C403,10u / 25V polarized,Capacitor_THT:CP_Radial_D6.3mm_P2.50mm,"Radial electrolytic 10uF 25V, D<=6.3mm P2.5mm",THT manual
C404,100n / 50V X7R,Capacitor_THT:C_Disc_D5.0mm_W2.5mm_P5.00mm,"100nF 50V X7R radial, 5mm lead pitch",THT manual
C502,10u / 25V BIPOLAR,Ardor_THT:CP_Bipolar_D6.3mm_P2.50mm,Nichicon UES1E100MDM,THT manual
R505,1kR / 1% 0.25W,Resistor_THT:R_Axial_DIN0207_L6.3mm_D2.5mm_P10.16mm_Horizontal,Axial metal film 1kΩ 1% 0.25W,THT manual
R506,100kR / 1% 0.25W,Resistor_THT:R_Axial_DIN0207_L6.3mm_D2.5mm_P10.16mm_Horizontal,Axial metal film 100kΩ 1% 0.25W,THT manual
